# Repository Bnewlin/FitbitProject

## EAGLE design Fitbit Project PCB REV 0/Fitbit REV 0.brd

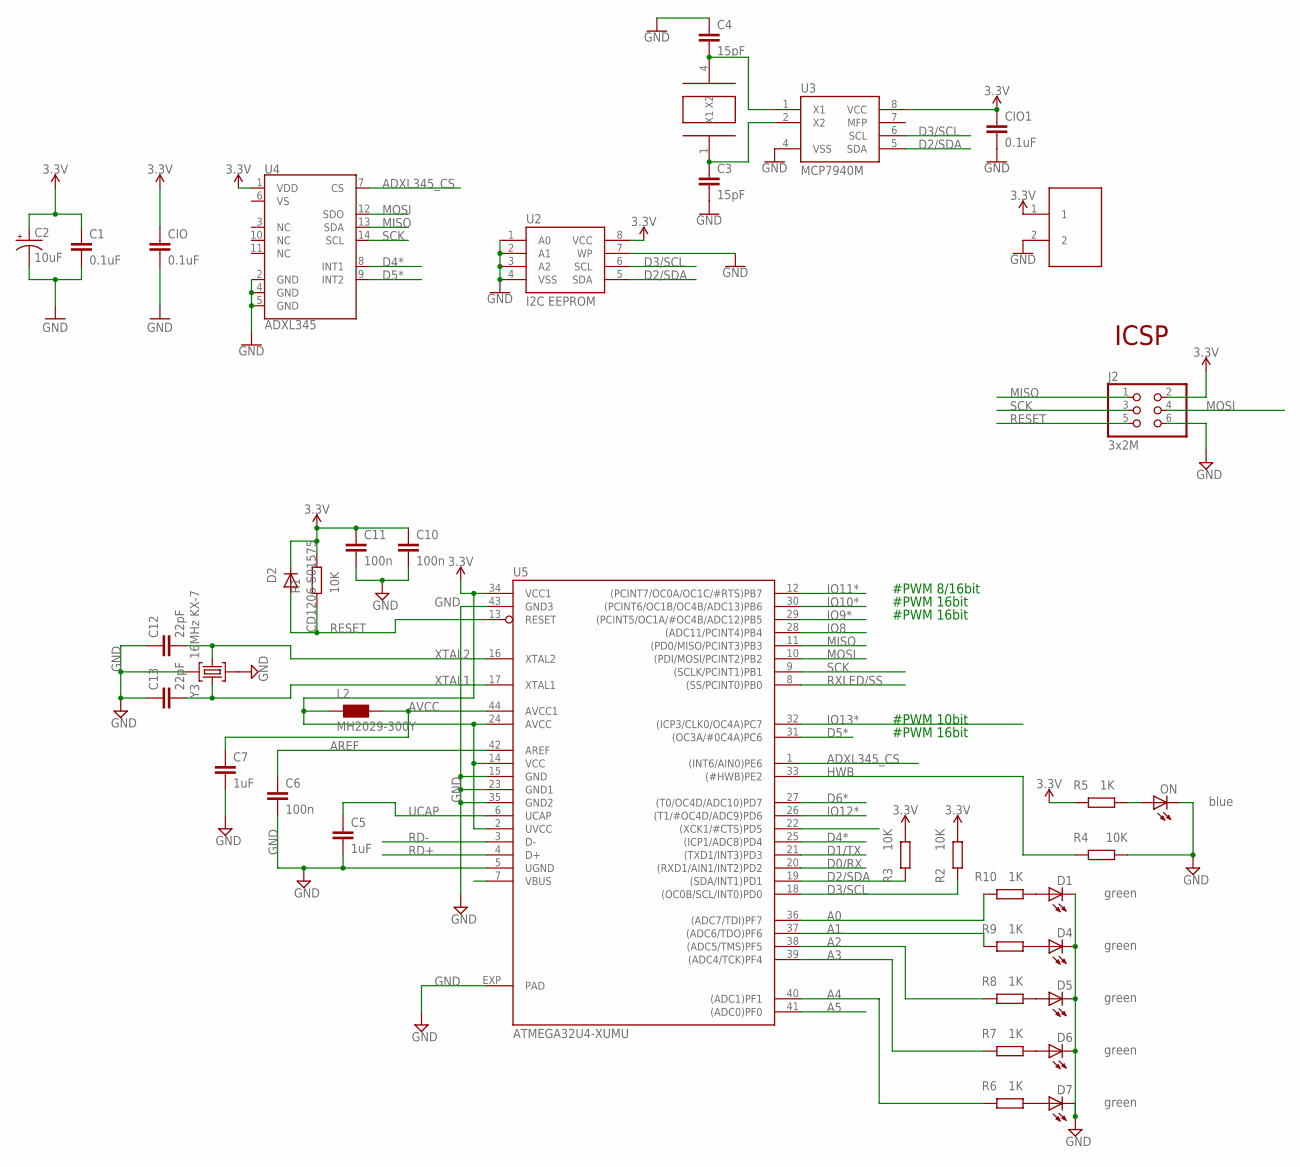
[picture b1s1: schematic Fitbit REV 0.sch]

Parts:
C1: 0.1uF; 0603-CAP
C2: 10uF; EIA3216
C3, C4: 15pF; C0402
C5, C7: 1uF; C0402
C6, C10, C11: 100n; C0402
C12, C13: 22pF; C0402
CIO, CIO1: 0.1uF; 0603-CAP
D1, D4, D5, D6, D7: green; CHIPLED_0805
D2: CD1206-S01575; MINIMELF
J1: S2B-PH-SM4-TB(LF)(SN)
J2: 3x2M; 2X03
L2: MH2029-300Y; 0805
ON: blue; CHIPLED_0805
R1, R2, R3, R4: 10K; R0402
R5, R6, R7, R8, R9, R10: 1K; R0402
U2: I2C EEPROM; SO08-EIAJ
U3: MCP7940M; MSOP8
U4: ADXL345; LGA-14
U5: ATMEGA32U4-XUMU; QFN44ML7X7
Y1: MC-146_32.7680KA
Y3: 16MHz KX-7; CRYSTAL-3.2-2.5

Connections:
3.3V: C1.1, C2.A (+), C10.1, C11.1, CIO.1, CIO1.1, D2.C, J1.1, J2.2, L2.1, R1.1, R2.2, R3.2, R5.1, U2.8 (VCC), U3.8 (VCC), U4.1 (VDD), U5.2 (UVCC), U5.14 (VCC), U5.24 (AVCC), U5.34 (VCC1)
A0: R10.1, U5.36 ((ADC7/TDI)PF7)
A1: R9.1, U5.37 ((ADC6/TDO)PF6)
A2: R8.1, U5.38 ((ADC5/TMS)PF5)
A3: R7.1, U5.39 ((ADC4/TCK)PF4)
A4: R6.1, U5.40 ((ADC1)PF1)
A5: U5.41 ((ADC0)PF0)
ADXL345_CS: U4.7 (CS), U5.1 ((INT6/AIN0)PE6)
AREF: C6.1, U5.42 (AREF)
AVCC: C7.1, L2.2, U5.44 (AVCC1)
D0/RX: U5.20 ((RXD1/AIN1/INT2)PD2)
D1/TX: U5.21 ((TXD1/INT3)PD3)
D2/SDA: R3.1, U2.5 (SDA), U3.5 (SDA), U5.19 ((SDA/INT1)PD1)
D3/SCL: R2.1, U2.6 (SCL), U3.6 (SCL), U5.18 ((OC0B/SCL/INT0)PD0)
D4*: U5.25 ((ICP1/ADC8)PD4)
D5*: U5.31 ((OC3A/#0C4A)PC6)
D6*: U5.27 ((T0/OC4D/ADC10)PD7)
GND: C1.2, C2.C (-), C3.2, C4.1, C5.2, C6.2, C7.2, C10.2, C11.2, C12.1, C13.1, CIO.2, CIO1.2, D1.C, D4.C, D5.C, D6.C, D7.C, J1.2, J2.6, ON.C, R4.2, U2.1 (A0), U2.2 (A1), U2.3 (A2), U2.4 (VSS), U2.7 (WP), U3.4 (VSS), U4.2 (GND), U4.4 (GND), U4.5 (GND), U5.5 (UGND), U5.15 (GND), U5.23 (GND1), U5.35 (GND2), U5.43 (GND3), U5.EXP (PAD), Y3.2 (GND), Y3.4 (GND)
HWB: R4.1, U5.33 ((#HWB)PE2)
IO8: U5.28 ((ADC11/PCINT4)PB4)
IO9*: U5.29 ((PCINT5/OC1A/#OC4B/ADC12)PB5)
IO10*: U5.30 ((PCINT6/OC1B/OC4B/ADC13)PB6)
IO11*: U5.12 ((PCINT7/OC0A/OC1C/#RTS)PB7)
IO12*: U5.26 ((T1/#OC4D/ADC9)PD6)
IO13*: U5.32 ((ICP3/CLK0/OC4A)PC7)
MISO: J2.1, U4.13 (SDA), U5.11 ((PD0/MISO/PCINT3)PB3)
MOSI: J2.4, U4.12 (SDO), U5.10 ((PDI/MOSI/PCINT2)PB2)
unnamed: D7.A, R6.2
unnamed: ON.A, R5.2
unnamed: D6.A, R7.2
unnamed: D5.A, R8.2
unnamed: D4.A, R9.2
unnamed: D1.A, R10.2
unnamed: C3.1, U3.2 (X2), Y1.1 (X1)
unnamed: C4.2, U3.1 (X1), Y1.4 (X2)
RD+: U5.4 (D+)
RD-: U5.3 (D-)
RESET: D2.A, J2.5, R1.2, U5.13 (RESET)
RXLED/SS: U5.8 ((SS/PCINT0)PB0)
SCK: J2.3, U4.14 (SCL), U5.9 ((SCLK/PCINT1)PB1)
TXLED: U5.22 ((XCK1/#CTS)PD5)
UCAP: C5.1, U5.6 (UCAP)
XTAL1: C13.2, U5.17 (XTAL1), Y3.3 (C2)
XTAL2: C12.2, U5.16 (XTAL2), Y3.1 (C1)

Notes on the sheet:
#PWM 16bit
#PWM 10bit
#PWM 8/16bit
ICSP

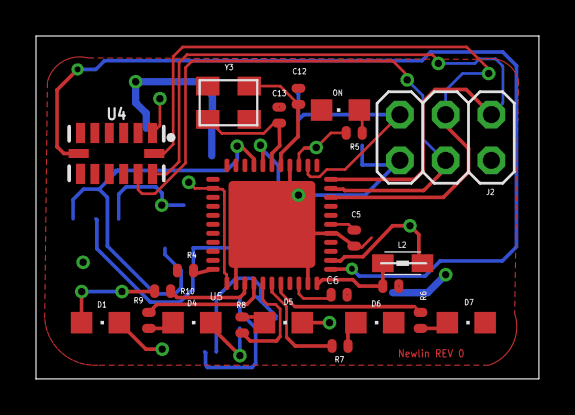
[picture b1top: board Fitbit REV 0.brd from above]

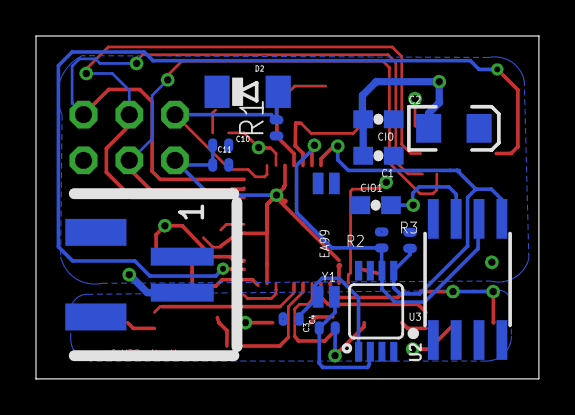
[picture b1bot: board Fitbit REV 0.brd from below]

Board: 2 copper layers, 27.9 x 19.1 mm, 39 parts (16 on the bottom side), 28 nets.

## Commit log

2017-06-21 Initial commit
    PCB board rev 0
    Test code

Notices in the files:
parts and their libraries:
SparkFun-IC-Memory: Licensing: Creative Commons ShareAlike 4.0 International - https://creativecommons.org/licenses/by-sa/4.0
